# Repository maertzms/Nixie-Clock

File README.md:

# Nixie-Clock
Six Digit clock using nixie tubes and a raspberry pi.
Custom boards were made and added with gerbers.

Please note, that while the gerbers and such will likely not match what the software will be doing, simply changing the pins used should fix that problem.

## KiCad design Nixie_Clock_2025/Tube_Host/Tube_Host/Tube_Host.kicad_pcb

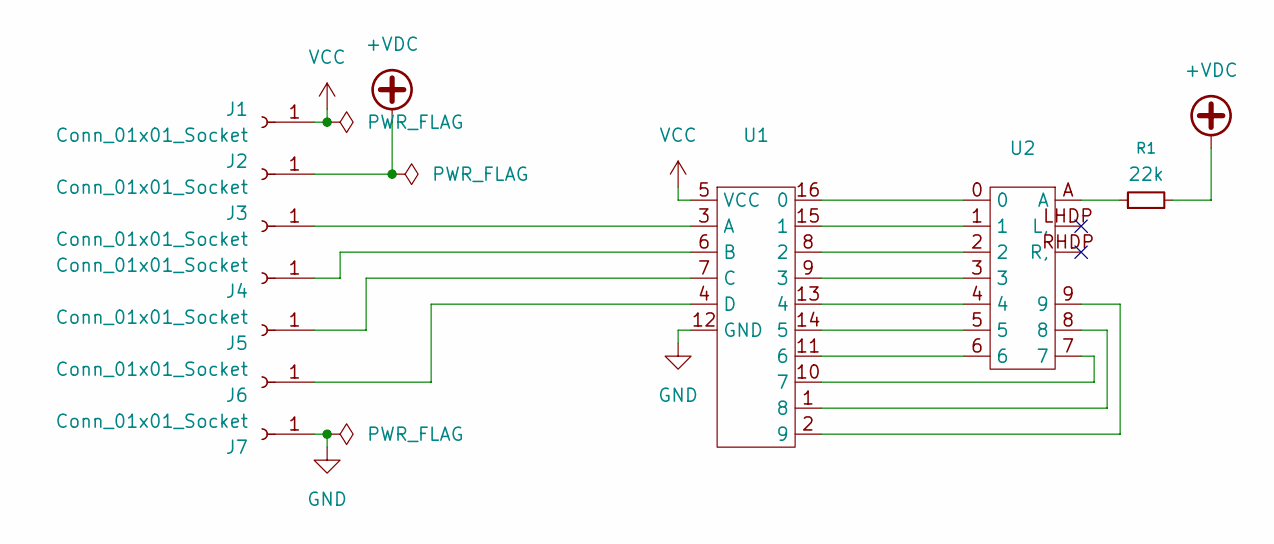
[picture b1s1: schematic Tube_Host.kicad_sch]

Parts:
J1, J2, J3, J4, J5, J6, J7: Conn_01x01_Socket; PinSocket_1x01_P2.54mm_Vertical
R1: 22k; R_0603_1608Metric
U1: K155ID1
U2: nixies-us-IN-14

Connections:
+VDC: J2.1, R1.2
GND: J7.1, U1.12 (GND)
unnamed: J3.1, U1.3 (A)
unnamed: J4.1, U1.6 (B)
unnamed: J5.1, U1.7 (C)
unnamed: J6.1, U1.4 (D)
unnamed: R1.1, U2.A
unnamed: U1.16 (0), U2.0
unnamed: U1.15 (1), U2.1
unnamed: U1.8 (2), U2.2
unnamed: U1.9 (3), U2.3
unnamed: U1.13 (4), U2.4
unnamed: U1.14 (5), U2.5
unnamed: U1.11 (6), U2.6
unnamed: U1.10 (7), U2.7
unnamed: U1.1 (8), U2.8
unnamed: U1.2 (9), U2.9
VCC: J1.1, U1.5 (VCC)

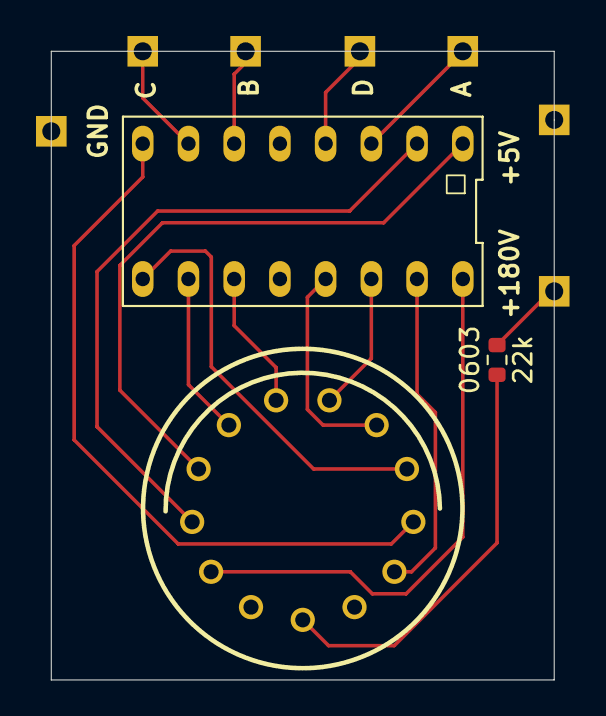
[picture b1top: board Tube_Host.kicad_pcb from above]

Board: 2 copper layers, 27.9 x 34.9 mm, 10 parts (0 on the bottom side), 18 nets.

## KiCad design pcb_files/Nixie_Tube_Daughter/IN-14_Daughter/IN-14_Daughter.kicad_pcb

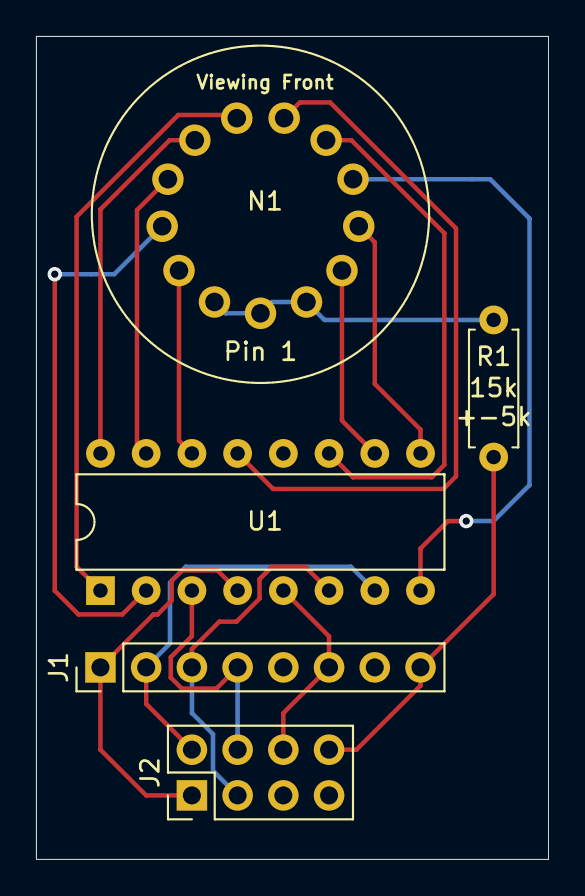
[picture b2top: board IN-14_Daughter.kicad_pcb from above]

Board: 2 copper layers, 28.4 x 45.7 mm, 5 parts (0 on the bottom side), 18 nets.

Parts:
J1: Conn_01x08_Male; PinHeader_1x08_P2.54mm_Vertical
J2: Conn_02x04_Counter_Clockwise; PinHeader_2x04_P2.54mm_Vertical
N1: IN-14; CPA_13
R1: 18k; R_Axial_DIN0207_L6.3mm_D2.5mm_P7.62mm_Horizontal
U1: 74141-DIP; DIP-16_W7.62mm

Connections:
GND: J1.5, J1.7, J2.5, J2.7, U1.12
unnamed: J1.1, J2.1, U1.4
unnamed: J1.2, J2.2, U1.7
unnamed: J1.3, J2.3, U1.6
unnamed: J1.4, J2.4, U1.3
unnamed: J1.8, J2.8, R1.1
unnamed: N1.1, N1.2, N1.13, R1.2
unnamed: N1.3, U1.14
unnamed: N1.4, U1.2
unnamed: N1.5, U1.15
unnamed: N1.6, U1.16
unnamed: N1.7, U1.1
unnamed: N1.8, U1.13
unnamed: N1.9, U1.11
unnamed: N1.10, U1.8
unnamed: N1.11, U1.9
unnamed: N1.12, U1.10
VCC: J1.6, J2.6, U1.5

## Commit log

2020-09-22 Removed old code files and added PCB files for a motherboard and for a removeable/replaceable daughter board. Code that will be run on a raspberry pi is clock.c.
2022-05-10 Finally got around to getting software control of the gpio pins
2022-05-10 Updated the readme to reflect that the software and hardware are very much out of sync.
2022-05-10 testing login
2022-05-10 removed the test file to continue login testing
2022-05-11 Login issues fixed, added TODO for progress tracking
2022-07-11 Refactored files into categorical folders
2022-07-11 removed memory leak check from todo list. Because it does not seem to be a thing in python (auto garbage collect)
2022-07-12 Added gitignore file to ignore all swap files, Updated gpio-ctl to have int to bits, bit locations and gracefull exit of loop.
2024-08-21 Add files via upload
    Work in progress on getting an STM32 to drive the clock. Clock to timer is 170MHz
2025-05-14 added 2025 version
2025-05-14 added downloaded references
2025-05-16 added precursor tube host footprint
